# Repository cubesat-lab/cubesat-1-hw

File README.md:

# cubesat-1-hw
Hardware design for the "CubeSat-1" project.

## Repository Structure
[docs](docs/) - Documentation \
└── [datasheets](docs/datasheets/) - MCUs and ASICs Datasheets \
[hardware](hardware/) - Hardware Design \
├── [libraries](hardware/libraries) - KiCad Libraries \
└── [obc](hardware/obc/) - OBC (On-Board Computer) KiCad Project \
[mechanical](mechanical) - Mechanical Design \
[tests](tests) - Tests

## KiCad File Formats
Read here information about [File Formats](https://dev-docs.kicad.org/en/file-formats/)

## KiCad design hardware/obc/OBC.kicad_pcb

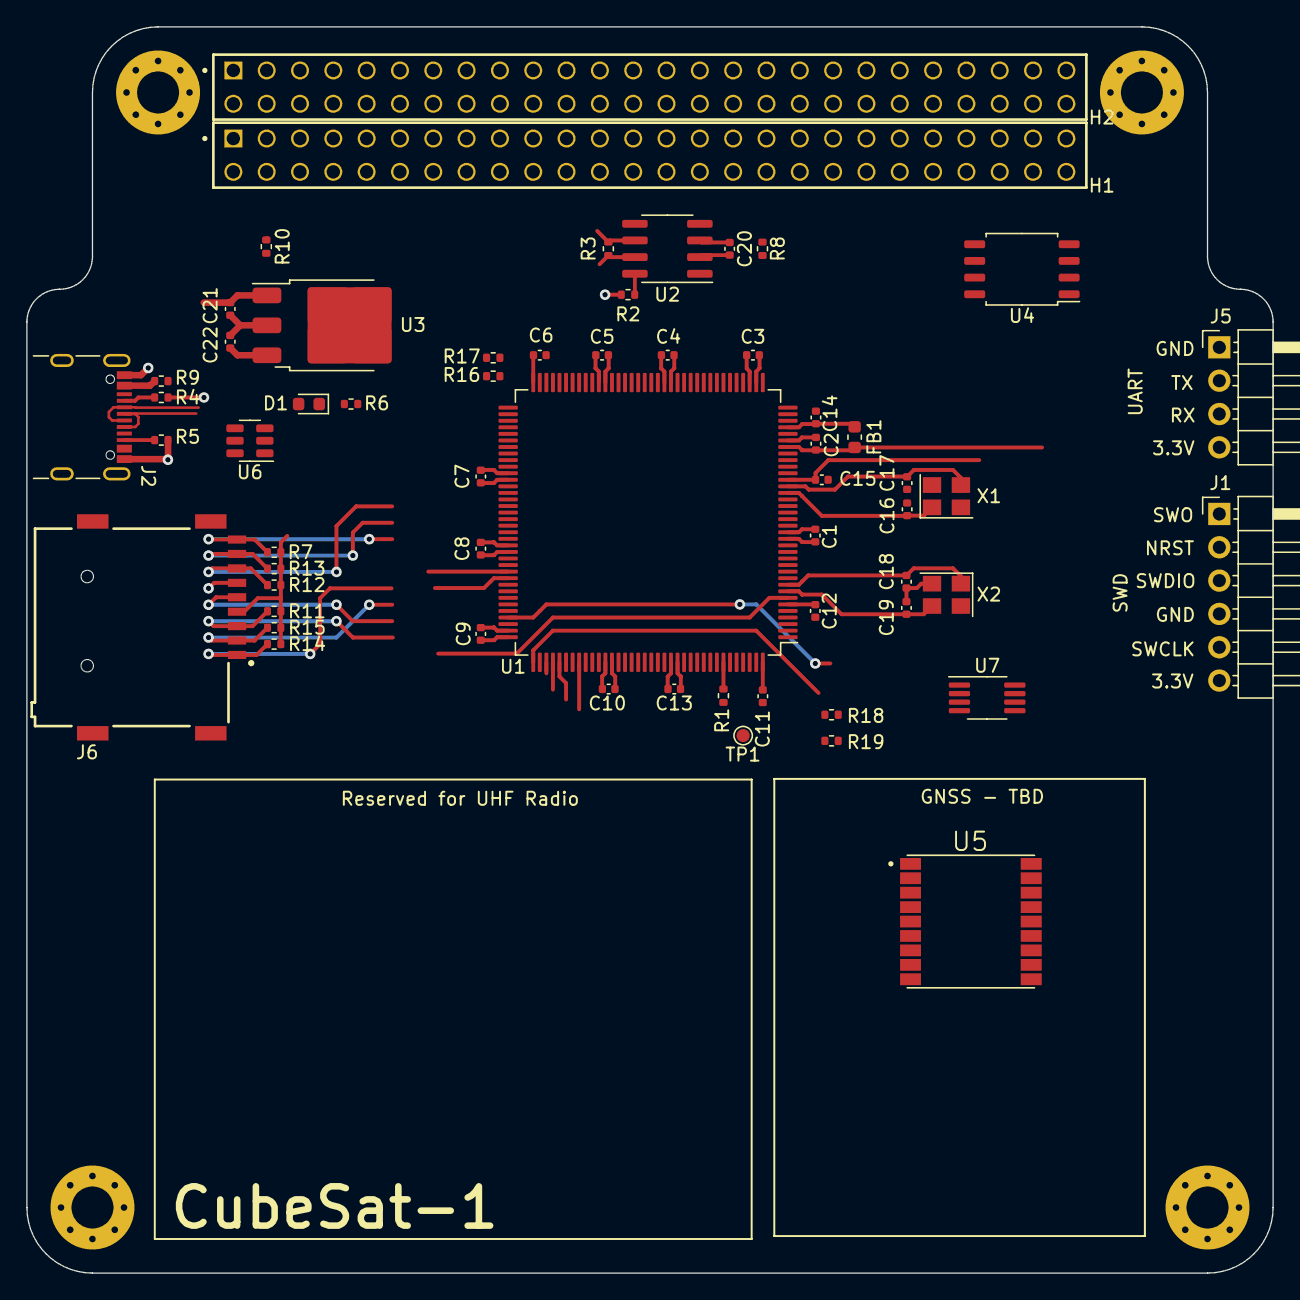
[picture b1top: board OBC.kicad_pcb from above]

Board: 2 copper layers, 95.0 x 95.0 mm, 63 parts (0 on the bottom side), 48 nets.

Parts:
C1, C2, C3, C4, C5, C6, C7, C8, C9, C10, C11, C12, C14, C15, C20: 100n; C_0402_1005Metric
C13: 4.7u; C_0402_1005Metric
C16, C17: 10p; C_0402_1005Metric
C18, C19: 2p; C_0402_1005Metric
C21: 1u; C_0402_1005Metric
C22: 2.2u; C_0402_1005Metric
D1: Green; LED_0603_1608Metric
FB1: 120R; L_0603_1608Metric
H1, H2: ESQ-126-39-G-D; SAMTEC_ESQ-126-39-G-D
J1: SWD; PinHeader_1x06_P2.54mm_Horizontal
J2: USB_C; USB_C_Receptacle_GCT_USB4105-xx-A_16P_TopMnt_Horizontal
J5: UART; PinHeader_1x04_P2.54mm_Horizontal
J6: Micro_SD_Card; GCT_MEM2075-00-140-01-A
MH1, MH2, MH3, MH4: MountingHole; MountingHole_3.2mm_M3_Pad_Via
R1, R2, R7: 10k; R_0402_1005Metric
R3: 120; R_0402_1005Metric
R4, R5: 5.1k; R_0402_1005Metric
R6: 1k; R_0402_1005Metric
R8, R9, R10: 0; R_0402_1005Metric
R11, R12, R13, R14, R15: 47k; R_0402_1005Metric
R16, R17, R18, R19: 2.2k; R_0402_1005Metric
TP1: BOOT0; TestPoint_Pad_D1.0mm
U1: STM32F767ZITx; LQFP-144_20x20mm_P0.5mm
U2: MCP2551-I-SN; SOIC-8_3.9x4.9mm_P1.27mm
U3: LD39150; TO-252-3_TabPin2
U4: CY15B102QN-50SXE; SOIC-8_5.23x5.23mm_P1.27mm
U5: TESEO-LIV3F
U6: USBLC6-2SC6; SOT-23-6
U7: MCP9804_MSOP; MSOP-8_3x3mm_P0.65mm
X1: 16MHz; Crystal_SMD_3225-4Pin_3.2x2.5mm
X2: 32.768kHz; Crystal_SMD_3225-4Pin_3.2x2.5mm

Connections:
+5V: C20.1, R8.1, U2.3 (VDD)
/Sheet: Connectors/CAN_H: H1.03, R3.1, U2.7 (CANH)
/Sheet: Connectors/CAN_L: H1.01, R3.2, U2.6 (CANL)
/Sheet: Connectors/GLO_I2C_SCL: H1.43, R16.1, U1.54 (I2C4_SCL)
/Sheet: Connectors/GLO_I2C_SDA: H1.41, R17.1, U1.55 (I2C4_SDA)
/Sheet: Connectors/SWCLK: J1.5, U1.109 (SYS_JTCK-SWCLK)
/Sheet: Connectors/SWDIO: J1.3, U1.105 (SYS_JTMS-SWDIO)
/Sheet: Connectors/SWO: J1.1, U1.133 (SYS_JTDO-SWO)
/Sheet: Connectors/UART_RX: J5.3, U1.76 (USART1_RX)
/Sheet: Connectors/UART_TX: J5.2, U1.75 (USART1_TX)
/Sheet: Connectors/USB_D+: U1.104 (USB_OTG_FS_DP), U6.1 (I/O1)
/Sheet: Connectors/USB_D-: U1.103 (USB_OTG_FS_DM), U6.3 (I/O2)
/Sheet: Connectors/VBUS_EPS: H1.47, R10.1
/Sheet: Connectors/VBUS_USB: J2.A4 (VBUS), J2.A9 (VBUS), J2.B4 (VBUS), J2.B9 (VBUS), R9.1, U6.5 (VBUS)
/Sheet: GNSS/GNSS_UART_RX: U1.122 (USART2_RX), U5.2 (TX)
/Sheet: GNSS/GNSS_UART_TX: U1.36 (USART2_TX), U5.3 (RX)
/Sheet: Memory/FRAM_CS: U1.40 (SPI1_NSS), U4.1 (CS)
/Sheet: Memory/FRAM_SCK: U1.41 (SPI1_SCK), U4.6 (SCK)
/Sheet: Memory/FRAM_SI: U1.43 (SPI1_MOSI), U4.5 (SI)
/Sheet: Memory/FRAM_SO: U1.42 (SPI1_MISO), U4.2 (SO)
/Sheet: Memory/SDMMC_CD: J6.P9 (CD), R7.1, U1.7 (PC13)
/Sheet: Memory/SDMMC_CK: J6.P5 (CLK), U1.113 (SDMMC1_CK)
/Sheet: Memory/SDMMC_CMD: J6.P3 (CMD), R11.1, U1.116 (SDMMC1_CMD)
/Sheet: Memory/SDMMC_D0: J6.P7 (DAT0), R12.1, U1.98 (SDMMC1_D0)
/Sheet: Memory/SDMMC_D1: J6.P8 (DAT1), R13.1, U1.99 (SDMMC1_D1)
/Sheet: Memory/SDMMC_D2: J6.P1 (DAT2), R14.1, U1.111 (SDMMC1_D2)
/Sheet: Memory/SDMMC_D3: J6.P2 (CD/DAT3), R15.1, U1.112 (SDMMC1_D3)
/Sheet: Microcontroller/NRST: C15.2, J1.2, U1.25 (NRST)
/Sheet: Microcontroller/PH0: C16.1, U1.23 (RCC_OSC_IN), X1.1
/Sheet: Microcontroller/PH1: C17.1, U1.24 (RCC_OSC_OUT), X1.3
/Sheet: Microcontroller/VDD_5V: C21.1, R8.2, R9.2, R10.2, U3.1 (VI)
/Sheet: PowerSupply/PWR_LED_K: D1.1 (K), R6.1
CAN_RX: U1.114 (CAN1_RX), U2.4 (RXD)
CAN_TX: U1.115 (CAN1_TX), U2.1 (TXD)
GND: C1.2, C2.2, C3.2, C4.2, C5.2, C6.2, C7.2, C8.2, C9.2, C10.2, C11.2, C12.2, C13.2, C14.2, C15.1, C16.2, C17.2, C18.2, C19.2, C20.2, C21.2, C22.2, H2.29, H2.30, H2.31, H2.32, J1.4, J2.A1 (GND), J2.A12 (GND), J2.B1 (GND), J2.B12 (GND), J5.1, J6.P6 (VSS), R1.1, R2.2, R4.2, R5.2, R6.2, U1.16 (VSS), U1.31 (VSSA), U1.38 (VSS), U1.51 (VSS), U1.61 (VSS), U1.83 (VSS), U1.94 (VSS), U1.107 (VSS), U1.120 (VSS), U1.130 (VSS), U2.2 (VSS), U3.2 (GND), U4.4 (GND), U5.1 (GND), U6.2 (GND), U7.4 (GND), X1.2, X1.4, X2.2, X2.4
I2C_SCL: R19.1, U1.11 (I2C2_SCL), U5.17 (SCL), U7.2 (SCL)
I2C_SDA: R18.1, U1.10 (I2C2_SDA), U5.16 (SDA), U7.1 (SDA)
unnamed: J2.A5 (CC1), R4.1
unnamed: J2.B5 (CC2), R5.1
unnamed: J2.A6 (D+), J2.B6 (D+), U6.6 (I/O1)
unnamed: J2.A7 (D-), J2.B7 (D-), U6.4 (I/O2)
unnamed: R1.2, TP1.1, U1.138 (BOOT0)
unnamed: C19.1, U1.8 (RCC_OSC32_IN), X2.3
unnamed: C18.1, U1.9 (RCC_OSC32_OUT), X2.1
unnamed: R2.1, U2.8 (Rs)
unnamed: U5.10 (GND_RF), U5.12 (GND_RF)
VDD: C1.1, C2.1, C3.1, C4.1, C5.1, C6.1, C7.1, C8.1, C9.1, C10.1, C11.1, C12.1, C13.1, C22.1, D1.2 (A), FB1.2, J1.6, J5.4, J6.P4 (VDD), R7.2, R11.2, R12.2, R13.2, R14.2, R15.2, R16.2, R17.2, R18.2, R19.2, U1.6 (VBAT), U1.17 (VDD), U1.30 (VDD), U1.39 (VDD), U1.52 (VDD), U1.62 (VDD), U1.72 (VDD), U1.84 (VDD), U1.95 (VDDUSB), U1.108 (VDD), U1.121 (VDDSDMMC), U1.131 (VDD), U1.144 (VDD), U3.3 (VO), U4.3 (WP), U4.8 (VDD), U7.8 (V_{DD})
VDDA: C14.1, FB1.1, U1.32 (VREF+), U1.33 (VDDA)

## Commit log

2024-02-26 Created directory structure. Added OBC KiCad project prototype
